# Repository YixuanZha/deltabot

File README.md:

# The Delta Bot

### What is the Delta Bot?
The Delta Bot is an open-source DIY robot AI platform that uses Radxa's single board computer, the [Rock 5B](https://radxa.com/products/rock5/5b/), a simple [camera module](https://www.raspberrypi.com/products/camera-module-v2/), Parallax's [Continuous Rotation Servo Motors](https://www.parallax.com/product/parallax-continuous-rotation-servo-factory-centered/), and the [RPLIDAR A1](https://www.slamtec.com/en/lidar/a1), a LIDAR camera by Slamtec.

### Purpose & Vision

### What can it do?

- 360 Degree 2D LiDAR Scans
- Precise Servo Movement 
- 1080p Video Capture
- Can be configured for Line Following, SLAM, Obstacle Detection, and more!

### Video Demonstration

*A video demonstration will be added once mechanical repairs are complete.*

<p align="center">
  
</p>

## How to get started
- For the list of components used refer to [List.md](List.md).
- To first set up your RADXA ROCK5B computer, and configure its GPIO pins refer to [Setup.md](Setup.md).
- For details on the DeltaBot schematic, pcb, and footprint library refer to [PCB.md](PCB.md).

### Installing core tools
```bash
sudo apt install libopencv-dev opencv-data python3-opencv
sudo apt install opencl-headers ocl-icd-opencl-dev
sudo apt install libgstreamer1.0-dev gstreamer1.0-plugins-base gstreamer1.0-plugins-good gstreamer1.0-tools
```
### Build the project
```bash
mkdir build
cd build
cmake ..
make
```

### Run the tests
If you want to test the wheels
```bash
./TestServoMotor <left_speed> <right_speed>
```
- `<left_speed>`: Speed value for the left servo motor(-10~10)
- `<right_speed>`: Speed value for the right servo motor(-10~10)
- `speed range`: -10 is full speed counterclockwise, 10 is full speed clockwise, 0 is no rotation
or
```bash
./TestSpeedChange
```
This test will demonstrate the motors accelerating, decelerating, and stopping automatically.

If you want to test the robot's movement
```bash
./TestBotMotion
```
This test allows you to control a robot using your keyboard in a terminal environment. You can drive the robot forward, backward, turn, adjust speed, stop, and exit the program using designated keys.
#### Controls
| Key | Action         |
|-----|---------------|
| W   | Forward       |
| S   | Backward      |
| A   | Turn Left     |
| D   | Turn Right    |
| R   | Speed Up      |
| F   | Decelerate    |
| X   | Stop          |
| Z   | Quit          |

#### Example

```text
Use the keyboard to control the bot: W(forward) S(backward) A(turn left) D(turn right) R(speed up) F(decelerate) X(stop) Z(quit)
Forward.....The speed is: 3
Turn left.....The speed is: 3
Speed up.....The speed is: 4
Stop.....
Quit.....
```
### Run the executable
```bash
./TestLineFollowing
```
You need to place the robot in a well-lit area with a high-contrast black line (e.g., electrical tape) on a white or light-colored background. The robot will then start its autonomous line-following behavior.

## Structure
The following outlines the DeltaBot's Architecture:

### Additional Mechanical Parts
Additional Mechanical Parts were designed in CAD and can be accessed [here](additional_files/deltabot.f3z).
These were used to secure the external components onto the Single PCB Chassis:

## Further Documentation
- [RADXA ROCK 5B Geekbenchv6 CPU Results](https://browser.geekbench.com/v6/cpu/11503510)
- [RADXA ROCK 5B Geekbenchv6 GPU (OpenCL) Results](https://browser.geekbench.com/v6/compute/4045302)
- Scripts from rplidar_rock file were adopteed from [here.](https://github.com/berndporr/rplidar_rpi)

## Credits
- Saleh AlMulla - 2721704A@student.gla.ac.uk
- Bernd Porr -  bernd.porr@glasgow.ac.uk
- Yixuan Zha - 2974642Z@student.gla.ac.uk

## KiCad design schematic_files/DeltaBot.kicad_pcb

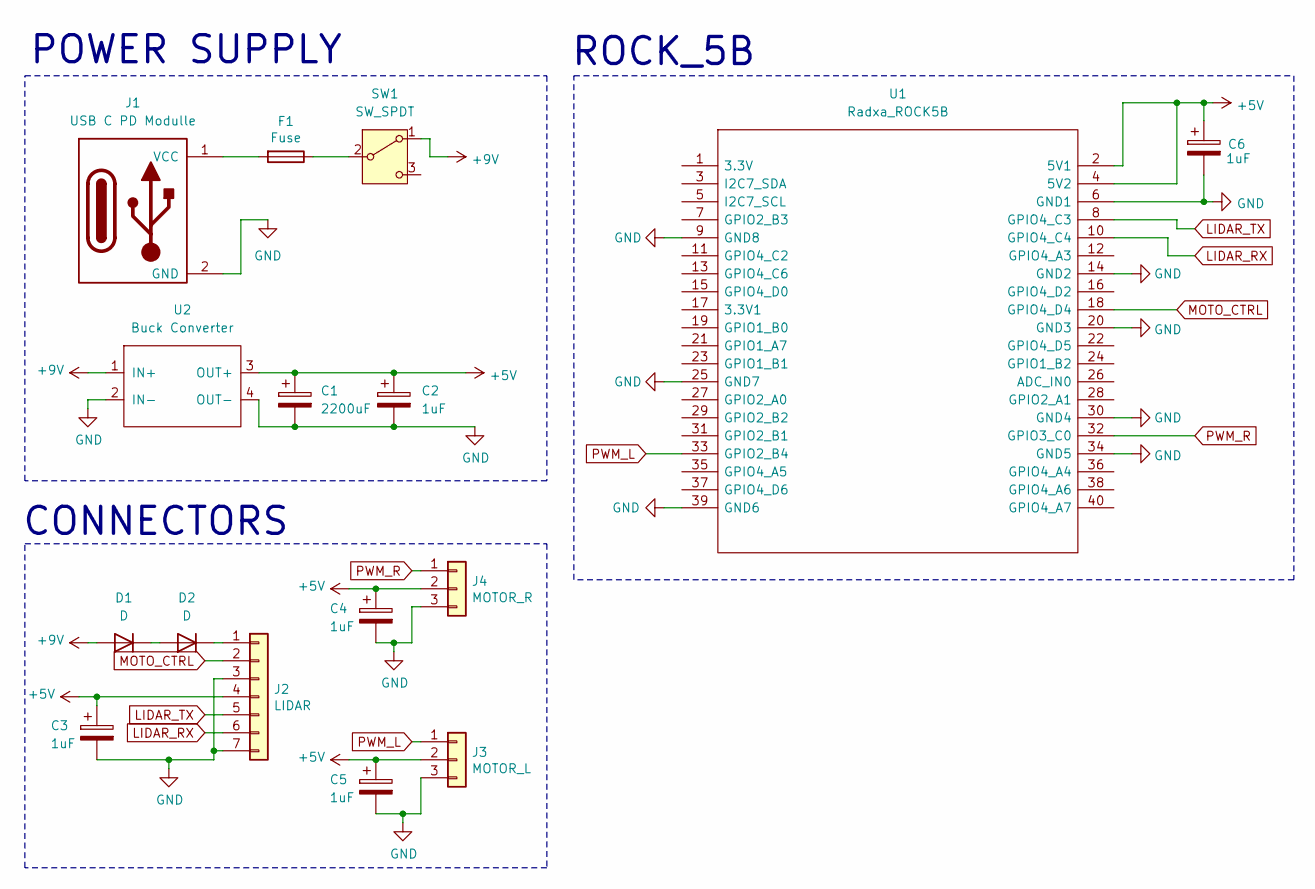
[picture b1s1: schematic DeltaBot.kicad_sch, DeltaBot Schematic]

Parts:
C1: 2200uF; CP_Radial_D12.5mm_P5.00mm
C2, C3, C4, C5, C6: 1uF; C_Disc_D3.0mm_W2.0mm_P2.50mm
D1, D2: D; D_DO-41_SOD81_P10.16mm_Horizontal
F1: Fuse; Fuseholder_Cylinder-5x20mm_Schurter_0031_8201_Horizontal_Op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
J1: USB C PD Modulle; USB_C
J2: LIDAR; PinHeader_1x07_P2.54mm_Vertical
J3: MOTOR_L; PinHeader_1x03_P2.54mm_Vertical
J4: MOTOR_R; PinHeader_1x03_P2.54mm_Vertical
SW1: SW_SPDT; TE_4-1825136-5
U1: Radxa_ROCK5B; ROCK_5B; Manufacturer_Part_Number ROCK5B V1.3
U2: Buck Converter; BUCK_CONV

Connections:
+5V: C1.1, C2.1, C3.1, C4.1, C5.1, C6.1, J2.4, J3.2, J4.2, U1.2 (5V1), U1.4 (5V2), U2.3 (OUT+)
+9V: D1.2 (A), SW1.1 (A), U2.1 (IN+)
GND: C1.2, C2.2, C3.2, C4.2, C5.2, C6.2, J1.2 (GND), J2.3, J2.7, J3.3, J4.3, U1.6 (GND1), U1.9 (GND8), U1.14 (GND2), U1.20 (GND3), U1.25 (GND7), U1.30 (GND4), U1.34 (GND5), U1.39 (GND6), U2.2 (IN-), U2.4 (OUT-)
LIDAR_RX: J2.6, U1.10 (GPIO4_C4)
LIDAR_TX: J2.5, U1.8 (GPIO4_C3)
MOTO_CTRL: J2.2, U1.18 (GPIO4_D4)
unnamed: D1.1 (K), D2.2 (A)
unnamed: D2.1 (K), J2.1
unnamed: F1.2, J1.1 (VCC)
unnamed: F1.1, SW1.2 (B)
PWM_L: J3.1, U1.33 (GPIO2_B4)
PWM_R: J4.1, U1.32 (GPIO3_C0)

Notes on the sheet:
POWER SUPPLY
CONNECTORS
ROCK_5B

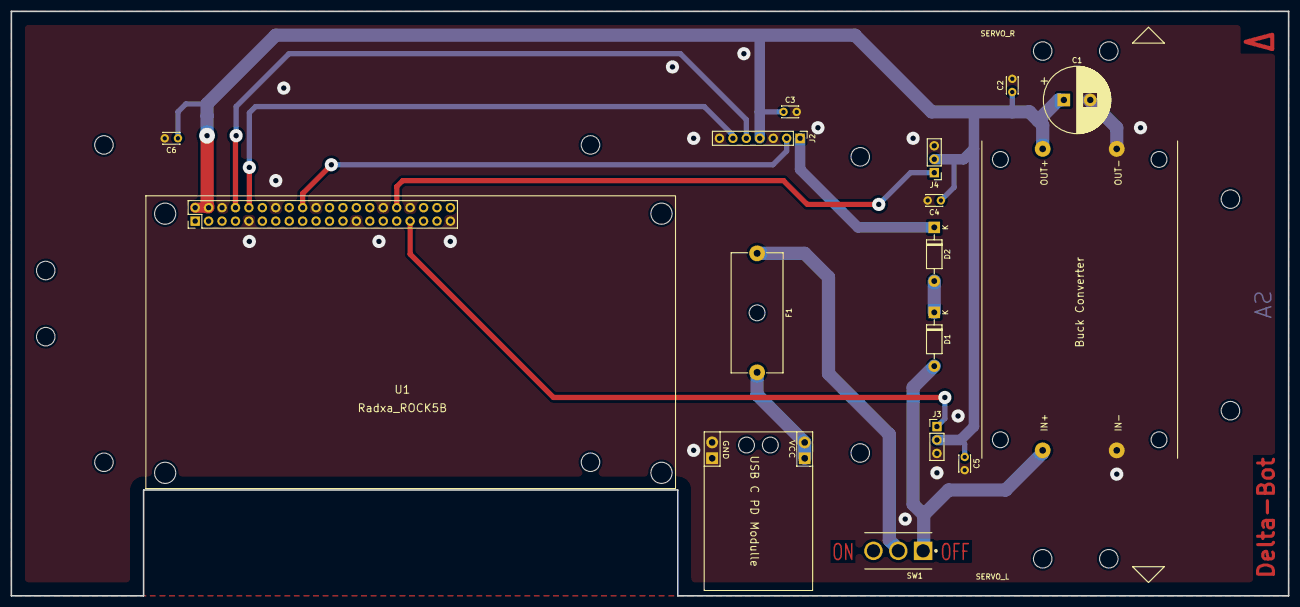
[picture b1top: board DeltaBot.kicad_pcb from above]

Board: 2 copper layers, 241.5 x 110.5 mm, 17 parts (0 on the bottom side), 12 nets.

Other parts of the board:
REF\: MountingHole_3.5mm

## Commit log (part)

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2025-01-16 Create Setting_up_ROCK5B
2025-01-16 Rename Setting_up_ROCK5B to Setting_up_ROCK5B.md
2025-01-16 Rename SetUp.md to Setup.md
2025-02-27 Rename PSU.md to PCB.md
2025-04-02 Rename IMG_5288 2.HEIC to images/IMG_5288 2.HEIC
2025-04-02 Rename DeltaBot.kicad_pcb to schematic_files/DeltaBot.kicad_pcb
2025-04-02 Rename DeltaBot.kicad_sch to schematic_files/DeltaBot.kicad_sch
2025-04-02 Rename sidebot.drawio.svg to images/sidebot.drawio.svg
2025-04-02 added photos
2025-04-02 Replace SVGs with PNGs
2025-04-02 final design architecture
2025-04-02 Changed from PDF to PNG
2025-04-02 Removed png transparency
2025-04-02 Rename Hardware_Architecture.drawio.png to Hardware_Architecture.png
2025-04-02 servo test code
2025-04-02 Rename servotest.py to scripts/servotest.py
2025-04-02 Rename rock 5B v1.f3z to additional_files/rock 5B v1.f3z
2025-04-09 corrected spelling error
2025-04-13 Rename scripts/a1lidarrpi.cpp to scripts/rplidar_rock/a1lidarrpi.cpp
2025-04-13 Rename scripts/a1lidarrpi.h to scripts/rplidar_rock/a1lidarrpi.h
2025-04-13 Rename printRPM.cpp to printRPM.cpp
2025-04-13 Rename scripts/printdata.cpp to scripts/rplidar_rock/printdata.cpp
2025-04-13 Rename Power_Flowchart.drawio-3.png to Power_Flowchart.drawio.png
2025-04-13 Update README.md
    added Geekbench results
2025-04-15 added gbr and drl files
2025-04-20 adjusted image label
2025-04-21 updated scripts
    updated code - last attempt
2025-04-21 Update README.md
    added open cl gpu benchmark test
2025-06-11 Remove PWM test scripts for cleanup
2025-06-11 Implement DeltaBot control and PWM functionality with servo motor settings
2025-06-23 Refactor CMakeLists.txt to include CaptureCameraFeed and update target dependencies
2025-06-23 Add CaptureCameraFeed class for camera feed handling
2025-06-23 Add TestCamera.cpp for testing CaptureCameraFeed functionality
2025-06-23 Remove frame flipping from CaptureCameraFeed::run to maintain original orientation
2025-06-23 Fix frame flipping direction in CaptureCameraFeed::run for correct display orientation
2025-06-23 Changr the display width to 1050
2025-06-23 Fix neutral time calculation in SpeedToHighTime for accurate speed mapping
2025-06-23 Fix neutral time value in SpeedToHighTime for accurate speed mapping
2025-06-23 Change the step size
2025-06-23 debug
2025-06-23 Increase step size in SpeedToHighTime methods for improved speed mapping accuracy
2025-06-29 Refactor main function in TestCamera to enhance camera initialization and error handling
2025-06-30 Update capture dimensions in TestCamera
2025-06-30 Update GStreamer pipeline to use rkvideoconvert for improved video processing
2025-06-30 Update GStreamer pipeline to use videoconvert for improved format handling
2025-06-30 Add camera functionality to DeltaBot class and improve initialization
2025-06-30 Enhance CaptureCameraFeed class with detailed constructor and destructor documentation, add error handling for GStreamer pipeline, and improve comments for clarity.
2025-07-02 Update CMakeLists.txt to add TestBotAndCamera executable
2025-07-02 Refactor CaptureCameraFeed class to implement thread control for video capture and add stop functionality
2025-07-02 Add TestBotAndCamera to control DeltaBot and manage camera feed
2025-07-02 Refactor input handling in TestBotAndCamera to use read() instead of getch() for non-blocking character input
2025-07-02 Refactor getch function to streamline character input handling and remove unused raw mode functions
2025-07-09 Add LineFollower executable and update CMakeLists.txt for CLDL sources
2025-07-09 Enhance CaptureCameraFeed class with thread-safe frame handling and error checks for captured frames
2025-07-09 Add SetMotorSpeed method to DeltaBot for controlling motor speeds
2025-07-09 Add TestLineFollowing.cpp for testing line following functionality with DeltaBot
2025-07-09 Remove CLDL subproject reference
2025-07-09 Squashed 'scripts/CLDL/' content from commit c4b6b64
    git-subtree-dir: scripts/CLDL
    git-subtree-split: c4b6b645cf7546b7b61a28e257724e0ea0cd9b89
2025-07-09 Add .gitignore file to exclude build artifacts and IDE configurations
2025-07-11 Fix speed initialization in LineFollower to 1.0f
2025-07-17 Refactor DeltaBot constructor to use unique_ptr for camera management and update StartCamera and StopCamera methods for proper camera handling
2025-07-17 Initialize DeltaBot with camera in TestLineFollowing for proper camera integration
2025-07-17 Fix learning rate initialization in LineFollower to 0.001 for improved training accuracy
2025-07-17 Update learning rate in LineFollower to 0.005 for improved training performance
2025-07-17 Comment out FPS calculation and display in CaptureCameraFeed run method for debugging purposes
2025-07-17 Enable FPS calculation and display in CaptureCameraFeed run method
2025-07-18 Refactor speed adjustment and error amplification in UpdateAndTrain for improved control responsiveness
2025-07-23 Fix typo in binary threshold variable name and correct error amplification calculation in LineFollower
2025-07-23 Remove unused main.cpp test file to clean up the project structure
2025-07-23 Update base speed in LineFollower for improved control responsiveness
2025-07-24 Refactor error propagation in UpdateAndTrain for improved training accuracy
2025-07-24 Refactor error handling in UpdateAndTrain to improve backpropagation accuracy
2025-07-24 Refactor backpropagation injection layers in UpdateAndTrain for enhanced error handling
2025-07-24 Refactor steering adjustments in LineFollower to implement PID control for improved accuracy
2025-07-24 Refactor LineFollower to enhance state management and input processing for improved line tracking
2025-07-24 Refactor LineFollower to enhance neural network initialization and improve error handling in line tracking
2025-07-24 Refactor CMakeLists.txt to remove unused test executables and streamline build configuration
2025-07-24 Refactor CaptureCameraFeed class to remove FPS calculation and display methods, streamline frame handling, and improve error handling during frame capture
2025-07-24 Remove TestBotAndCamera and TestCamera files to clean up unused test code
2025-07-24 Refactor ServoMotorSetting to clarify neutral time comments and correct documentation for speed-to-high time calculations
2025-07-25 Adjust base speed and derivative gain parameters in LineFollower for improved control responsiveness
2025-07-25 Adjust ROI segment positions in ProcessFrameAndGetInputs for improved frame analysis
2025-07-25 Adjust base speed in LineFollower for improved control responsiveness
2025-07-25 Fix base_speed initialization in LineFollower for correct float representation
2025-07-25 Adjust controller gains in LineFollower for improved performance
2025-07-25 Remove destructor declaration from LineFollower class
2025-07-25 Adjust controller gains and update ROI rectangles in LineFollower for improved tracking accuracy
2025-07-25 Update base_speed in LineFollower to optimize performance
2025-07-25 Adjust base_speed in LineFollower to improve performance
2025-07-26 Refactor LineFollower controller parameters and improve adaptive thresholding for enhanced tracking accuracy
2025-07-26 Add binary_threshold parameter for improved image processing in LineFollower
2025-07-26 Comment out heading error integral calculations in LineFollower to simplify control logic
2025-07-26 Refactor heading error integral calculations in LineFollower for improved control logic
2025-07-26 Add signal handling for graceful shutdown in LineFollower
2025-07-26 Initialize shutdown flag for graceful shutdown handling in LineFollower
2025-07-26 Update controller gains for improved line following performance
2025-07-26 Adjust proportional gain to 1.5f for improved line following control
2025-07-26 Update integral gain to 0.02f for improved line following control
2025-07-26 Update integral gain to 0.03f for improved line following control
2025-07-26 Update base speed to 2.5f for improved line following performance
2025-07-26 Add last_process_frame_id to track frame processing in LineFollower
2025-07-26 Initialize frame_id in CaptureCameraFeed and update its value during frame capture
2025-07-28 Adjust controller gains for improved line following stability
2025-07-28 Adjust integral gain in LineFollower for improved control response
2025-07-28 Refactor frame processing to use HSV color space for improved binary image generation
2025-07-28 Adjust upper black threshold in HSV color space for improved frame processing
2025-07-29 Refine upper black threshold in HSV color space for improved frame processing
2025-07-29 Adjust heading gain for improved line following performance
2025-07-29 Adjust integral gain for improved line following performance
2025-07-29 Add comments to clarify frame ID tracking and FPS calculation methods
2025-07-29 add a null kernerl file
2025-07-29 Add OpenCL support to Net class with initialization and kernel building
2025-07-29 Add initial OpenCL kernel file for CLDL processing
2025-07-29 Add OpenCL kernel file handling in CMakeLists.txt
2025-07-30 Add OpenCL buffer members to Layer class for kernel processing
2025-07-30 Refactor Net class to improve OpenCL integration and add custom backpropagation method
2025-07-30 Enhance OpenCL integration by releasing resources in destructor, updating kernel creation, and implementing custom forward and backward propagation methods
2025-07-30 Refactor neural network initialization and backpropagation in LineFollower class, adding OpenCL buffer for target output
2025-07-30 Fix typo in kernel function name for output error calculation
2025-07-30 Fix typo in calculate_output_error_kernel function name
2025-07-30 Refactor Layer class constructor to remove numBuses parameter and simplify initialization
2025-07-30 Enhance Net constructor with OpenCL initialization logging and improve code formatting
2025-07-30 Remove unnecessary blank line in Net constructor for improved readability
2025-07-30 Fix kernel argument types in customBackProp and updateWeights methods for correct data handling
2025-07-30 Fix global work size calculation in updateWeights method for correct kernel execution
2025-07-30 Add missing CMAKE_BUILD_TYPE setting in CMakeLists.txt for consistent build configuration
2025-07-30 Initialize net_input_buffer to nullptr for safer memory management
2025-07-30 Update error calculation in UpdateAndTrain method for improved training accuracy
2025-07-31 Add OpenCL target compile definitions for improved compatibility
2025-07-31 Refactor customBackProp method and add injectErrorDirectly for improved error handling
2025-07-31 Refactor UpdateAndTrain method to simplify error handling and backpropagation logic
2025-07-31 Fix error_gain value in LineFollower class for improved control response
2025-07-31 Reset controller gains to zero for derivative, heading, and integral adjustments
2025-07-31 Fix learning rate value in LineFollower class for improved control response
2025-07-31 Fix learning rate and error gain values in LineFollower class for improved control response
2025-07-31 Fix proportional gain value in LineFollower class for improved control response
2025-07-31 Fix heading gain value in LineFollower class for improved control response
2025-07-31 Update proportional gain value in LineFollower class for improved control response
2025-07-31 Update derivative gain value in LineFollower class for improved control response
2025-07-31 Update derivative and integral gain values in LineFollower class for improved control response
2025-07-31 Update base speed and controller gain values in LineFollower class for improved performance
2025-07-31 Update base speed in LineFollower class to correct value for improved performance
2025-07-31 Refactor controller parameters in LineFollower class for clarity and consistency
2025-08-01 Adjust upper black color range in ProcessFrameAndGetInputs for improved accuracy in binary image creation
2025-08-01 Update base speed in LineFollower class to improve performance
2025-08-01 Add OpenCL kernel comments and initialize buffers in Net class
2025-08-03 Update README.md with installation instructions, testing commands, and control guide for the Delta Bot
